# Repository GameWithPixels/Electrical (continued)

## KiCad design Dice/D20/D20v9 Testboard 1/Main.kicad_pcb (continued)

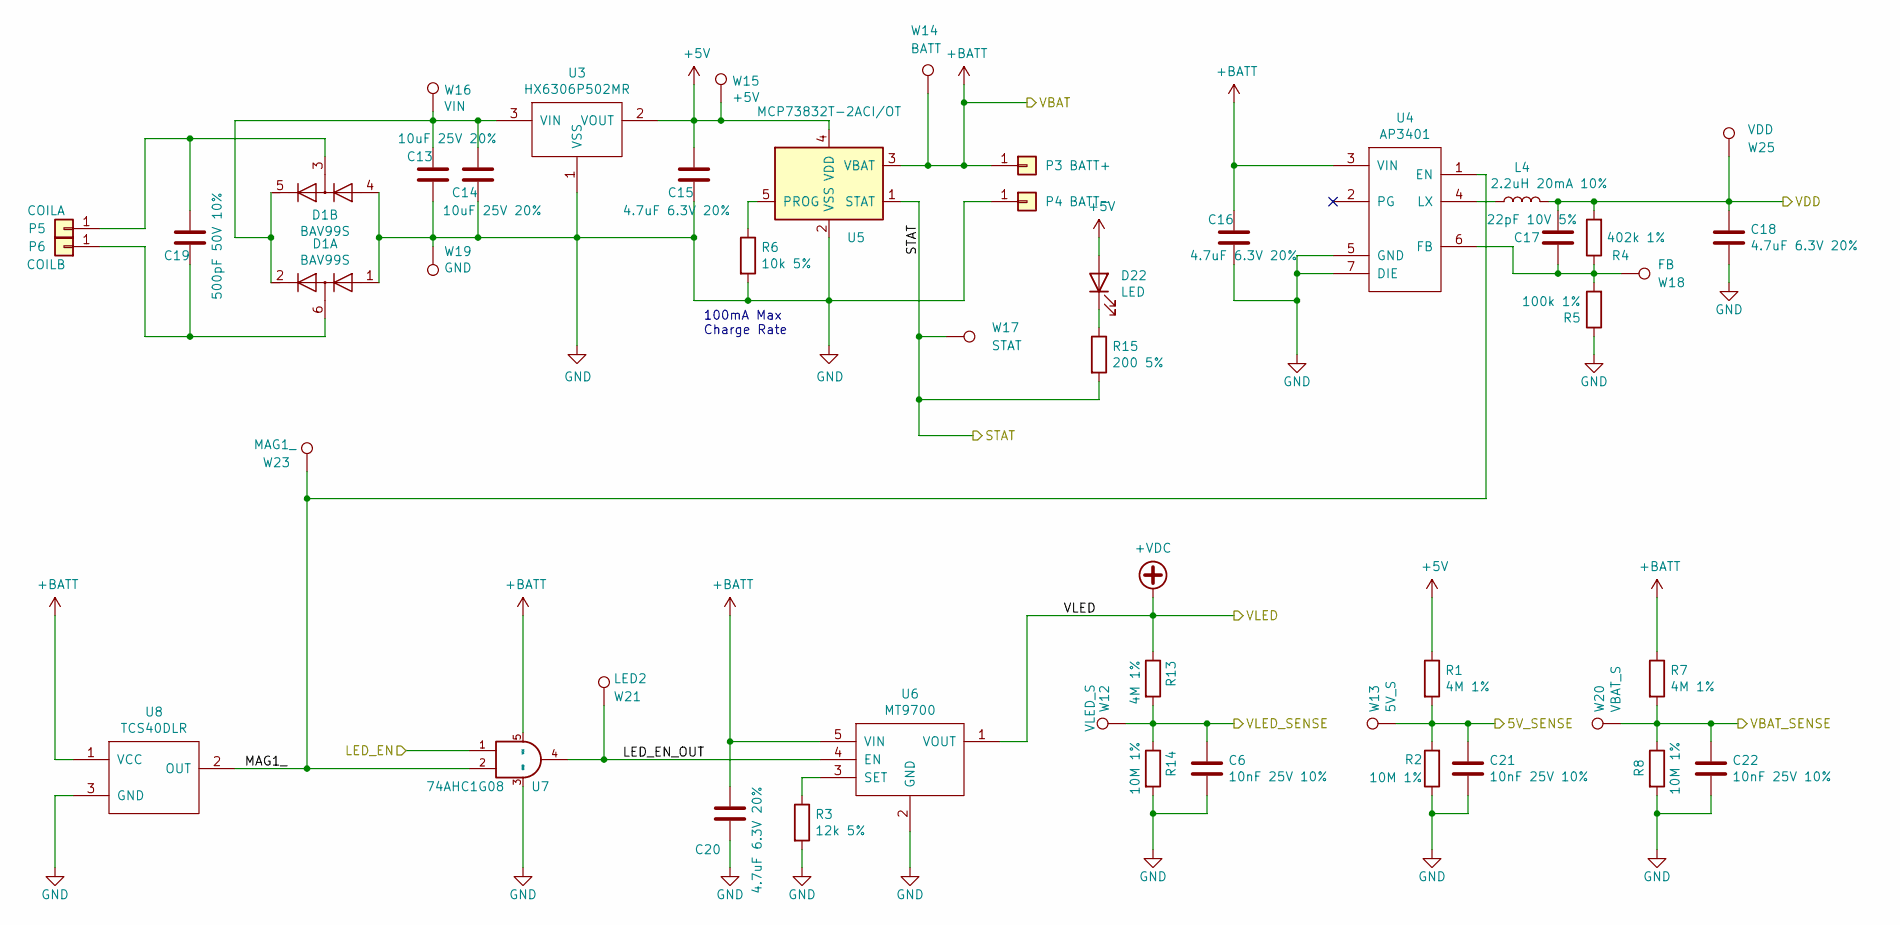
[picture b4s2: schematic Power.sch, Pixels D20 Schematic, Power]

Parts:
C6, C21, C22: 10nF 25V 10%; C_0402_1005Metric; Manufacturer Part Number AC0402KPX7R9BB103
C13, C14: 10uF 25V 20%; C_0805_2012Metric; Manufacturer Part Number CL21A106KAYNNNG
C15, C16, C18, C20: 4.7uF 6.3V 20%; C_0603_1608Metric; Manufacturer Part Number CL10A475MQ8NNNC
C17: 22pF 10V 5%; C_0402_1005Metric; Manufacturer Part Number CC0402JRNPO9BN220
C19: 500pF 50V 10%; C_0402_1005Metric; Manufacturer Part Number 04025C501KAT2A
D1: BAV99S; SOT-363_SC-70-6; Manufacturer Part Number BAV99SH6327XTSA1
D22: LED; LED_0402_1005Metric; Manufacturer Part Number IR19-21C/TR8
L4: 2.2uH 20mA 10%; L_0805_2012Metric; Manufacturer Part Number CV201210-2R2K
P3: BATT+; BatteryConnector
P4: BATT-; BatteryConnector
P5: COILA; TestPoint_THTPad_D1.5mm_Drill0.7mm
P6: COILB; TestPoint_THTPad_D1.5mm_Drill0.7mm
R1, R7, R13: 4M 1%; R_0402_1005Metric; Manufacturer Part Number CRCW04024M02FKED
R2, R8, R14: 10M 1%; R_0402_1005Metric; Manufacturer Part Number SFR01MZPJ106
R3: 12k 5%; R_0402_1005Metric; Manufacturer Part Number RCS040212K0FKED
R4: 402k 1%; R_0402_1005Metric; Manufacturer Part Number ERJ-2RKF4023X
R5: 100k 1%; R_0402_1005Metric; Manufacturer Part Number CRCW0402100KFKEDC
R6: 10k 5%; R_0402_1005Metric; Manufacturer Part Number CRCW040210K0FKEDC
R15: 200 5%; R_0402_1005Metric; Manufacturer Part Number CRCW0402200RJNED
U3: HX6306P502MR; SOT-23; Manufacturer Part Number HX6306P502MR
U4: AP3401; DFN-6-1EP_2x2mm_P0.65mm_EP1x1.6mm; Manufacturer Part Number AP3401DNTR-G1
U5: MCP73832T-2ACI/OT; SOT-23-5; Manufacturer Part Number MCP73832T-2ACI/OT
U6: MT9700; SOT-23-5; Manufacturer Part Number MT9700
U7: 74AHC1G08; SOT-353_SC-70-5; Manufacturer Part Number SN74AHC1G08DCKR
U8: TCS40DLR; SOT-23; Manufacturer Part Number TCS40DLR,LF
W12: VLED_S; TEST_PIN
W13: 5V_S; TEST_PIN
W14: BATT; TEST_PIN
W15: +5V; TEST_PIN
W16: VIN; TEST_PIN
W17: STAT; TEST_PIN
W18: FB; TEST_PIN
W19: GND; TEST_PIN
W20: VBAT_S; TEST_PIN
W21: LED2; TEST_PIN
W23: MAG1_; TEST_PIN
W25: VDD; TEST_PIN

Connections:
+5V: C15.1, D22.2 (A), R1.1, U3.2 (VOUT), U5.4 (VDD), W15.1
/5V_SENSE: C21.1, R1.2, R2.2, W13.1; also elsewhere on the board
/LED_EN: U7.1; also elsewhere on the board
/Power/LED_EN_OUT: U6.4 (EN), U7.4, W21.1
/Power/MAG1_: U4.1 (EN), U7.2, U8.2 (OUT), W23.1
/STATS: R15.2, U5.1 (STAT), W17.1; also elsewhere on the board
/VBAT_SENSE: C22.1, R7.2, R8.1, W20.1; also elsewhere on the board
/VLED_SENSE: C6.1, R13.2, R14.1, W12.1; also elsewhere on the board
GND: C6.2, C13.2, C14.2, C15.2, C16.2, C18.2, C20.2, C21.2, C22.2, D1.1 (A1), D1.4 (A3), P4.1, R2.1, R3.2, R5.1, R6.2, R8.2, R14.2, U3.1 (VSS), U4.5 (GND), U4.7 (DIE), U5.2 (VSS), U6.2 (GND), U7.3 (GND), U8.3 (GND), W19.1; also elsewhere on the board
unnamed: C13.1, C14.1, D1.2 (K2), D1.5 (K4), U3.3 (VIN), W16.1
unnamed: C17.2, R4.1, R5.2, U4.6 (FB), W18.1
unnamed: C19.1, D1.3 (K1A2), P5.1
unnamed: C19.2, D1.6 (K3A4), P6.1
unnamed: D22.1 (K), R15.1
unnamed: L4.1, U4.4 (LX)
unnamed: R3.1, U6.3 (SET)
unnamed: R6.1, U5.5 (PROG)
VBAT: C16.1, C20.1, P3.1, R7.1, U4.3 (VIN), U5.3 (VBAT), U6.5 (VIN), U7.5 (VCC), U8.1 (VCC), W14.1; also elsewhere on the board
VDD: C17.1, C18.1, L4.2, R4.2, W25.1; also elsewhere on the board
VLED: R13.1, U6.1 (VOUT); also elsewhere on the board

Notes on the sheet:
100mA Max Charge Rate

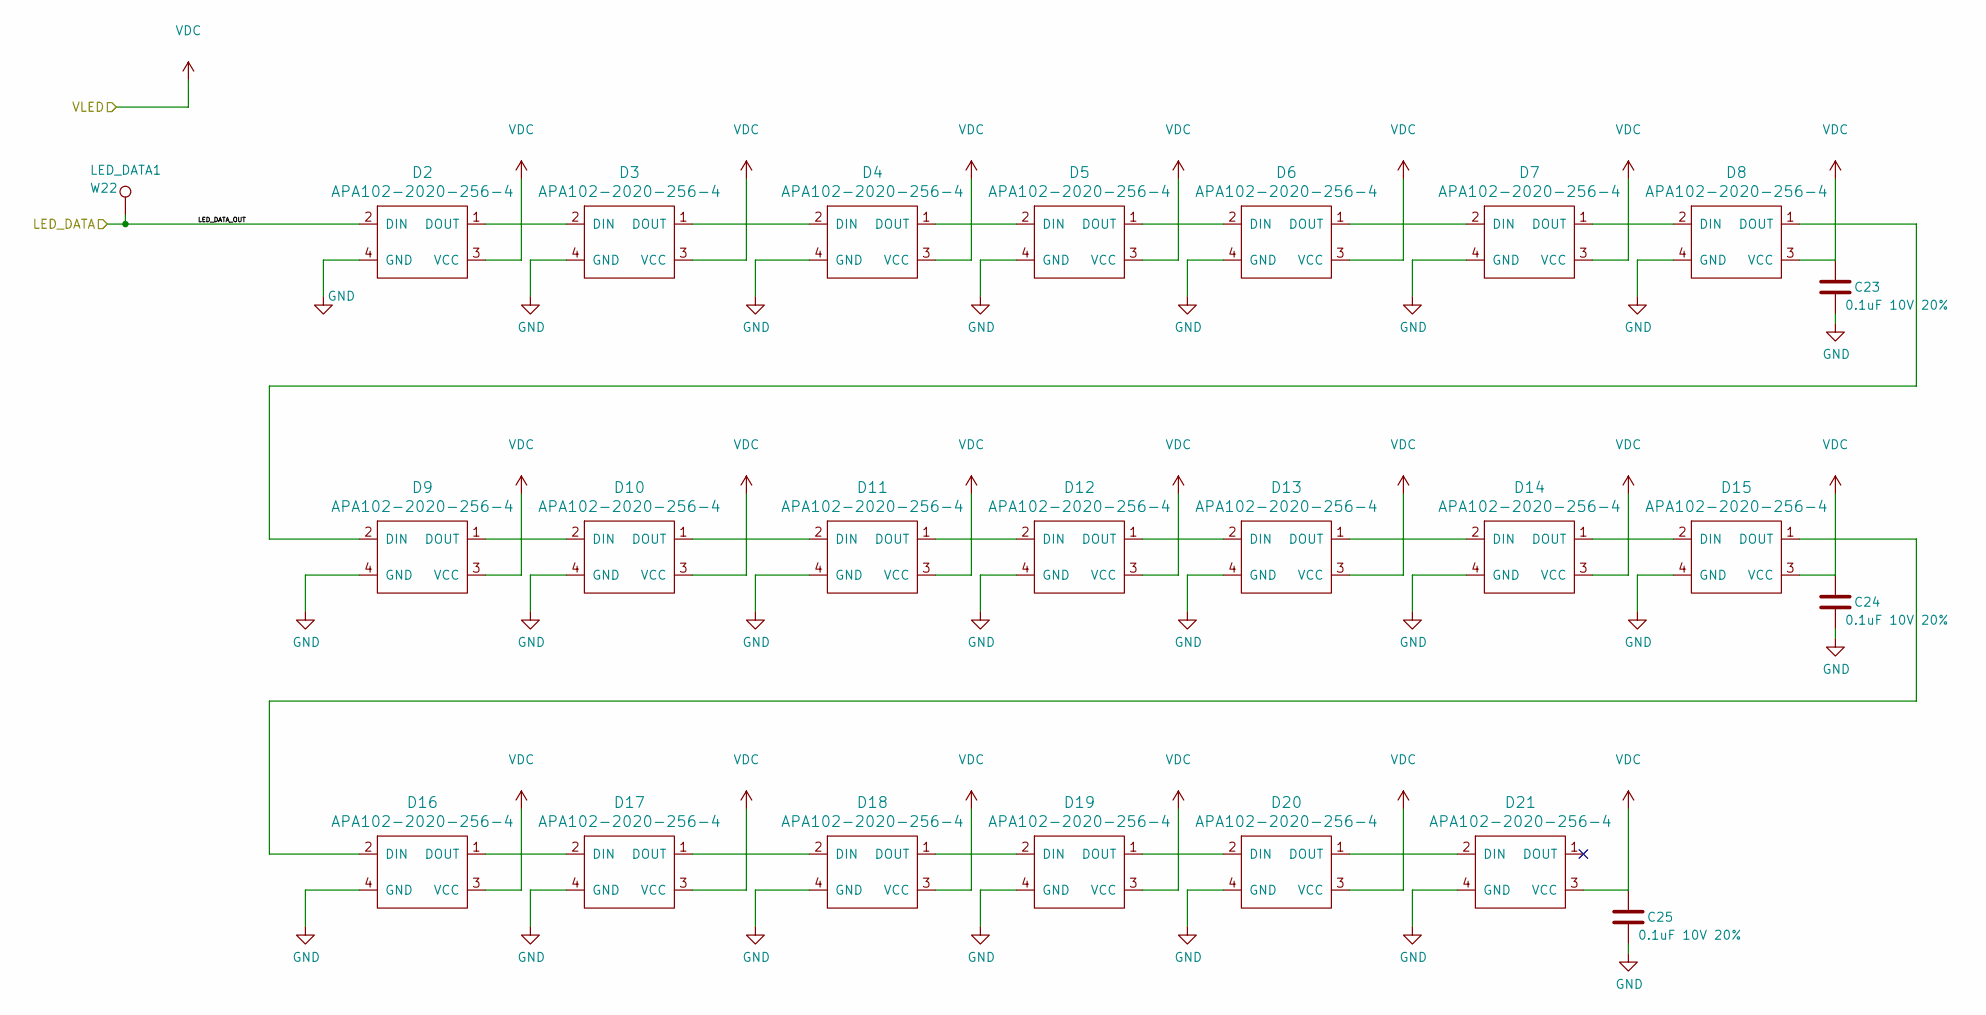
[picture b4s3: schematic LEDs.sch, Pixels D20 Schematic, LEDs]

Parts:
C23, C24, C25: 0.1uF 10V 20%; C_0402_1005Metric; Manufacturer Part Number GRM155R61H104KE19D
D2, D3, D4, D5, D6, D7, D8, D9, D10, D11, D12, D13, D14, D15, D16, D17, D18, D19, D20, D21: APA102-2020-256-4; Manufacturer Part Number APA-102-2020
W22: LED_DATA1; TEST_PIN

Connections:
/LED_DATA: D2.2 (DIN), W22.1; also elsewhere on the board
GND: C23.2, C24.2, C25.2, D2.4 (GND), D3.4 (GND), D4.4 (GND), D5.4 (GND), D6.4 (GND), D7.4 (GND), D8.4 (GND), D9.4 (GND), D10.4 (GND), D11.4 (GND), D12.4 (GND), D13.4 (GND), D14.4 (GND), D15.4 (GND), D16.4 (GND), D17.4 (GND), D18.4 (GND), D19.4 (GND), D20.4 (GND), D21.4 (GND); also elsewhere on the board
unnamed: D2.1 (DOUT), D3.2 (DIN)
unnamed: D3.1 (DOUT), D4.2 (DIN)
unnamed: D4.1 (DOUT), D5.2 (DIN)
unnamed: D5.1 (DOUT), D6.2 (DIN)
unnamed: D6.1 (DOUT), D7.2 (DIN)
unnamed: D7.1 (DOUT), D8.2 (DIN)
unnamed: D8.1 (DOUT), D9.2 (DIN)
unnamed: D10.1 (DOUT), D11.2 (DIN)
unnamed: D9.1 (DOUT), D10.2 (DIN)
unnamed: D11.1 (DOUT), D12.2 (DIN)
unnamed: D12.1 (DOUT), D13.2 (DIN)
unnamed: D13.1 (DOUT), D14.2 (DIN)
unnamed: D14.1 (DOUT), D15.2 (DIN)
unnamed: D15.1 (DOUT), D16.2 (DIN)
unnamed: D16.1 (DOUT), D17.2 (DIN)
unnamed: D17.1 (DOUT), D18.2 (DIN)
unnamed: D18.1 (DOUT), D19.2 (DIN)
unnamed: D19.1 (DOUT), D20.2 (DIN)
unnamed: D20.1 (DOUT), D21.2 (DIN)
VLED: C23.1, C24.1, C25.1, D2.3 (VCC), D3.3 (VCC), D4.3 (VCC), D5.3 (VCC), D6.3 (VCC), D7.3 (VCC), D8.3 (VCC), D9.3 (VCC), D10.3 (VCC), D11.3 (VCC), D12.3 (VCC), D13.3 (VCC), D14.3 (VCC), D15.3 (VCC), D16.3 (VCC), D17.3 (VCC), D18.3 (VCC), D19.3 (VCC), D20.3 (VCC), D21.3 (VCC); also elsewhere on the board

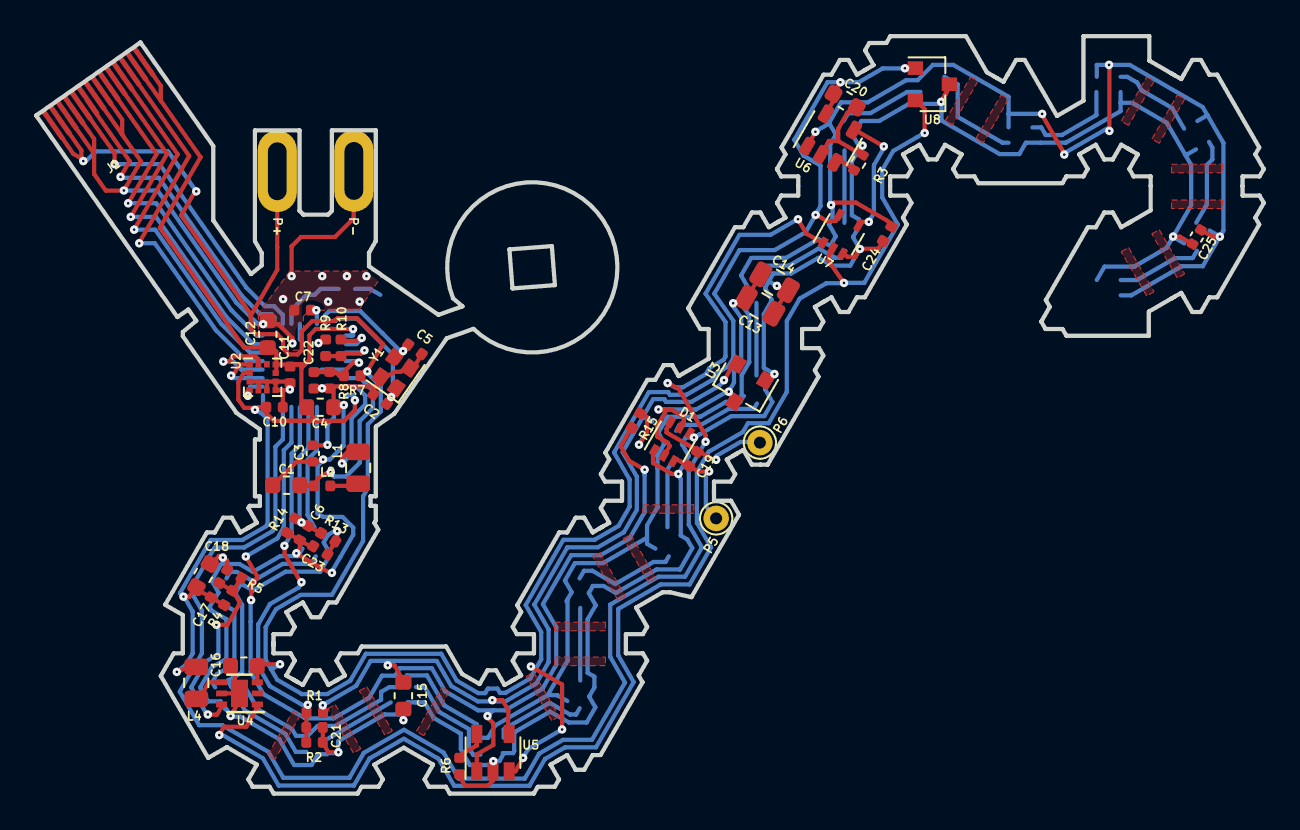
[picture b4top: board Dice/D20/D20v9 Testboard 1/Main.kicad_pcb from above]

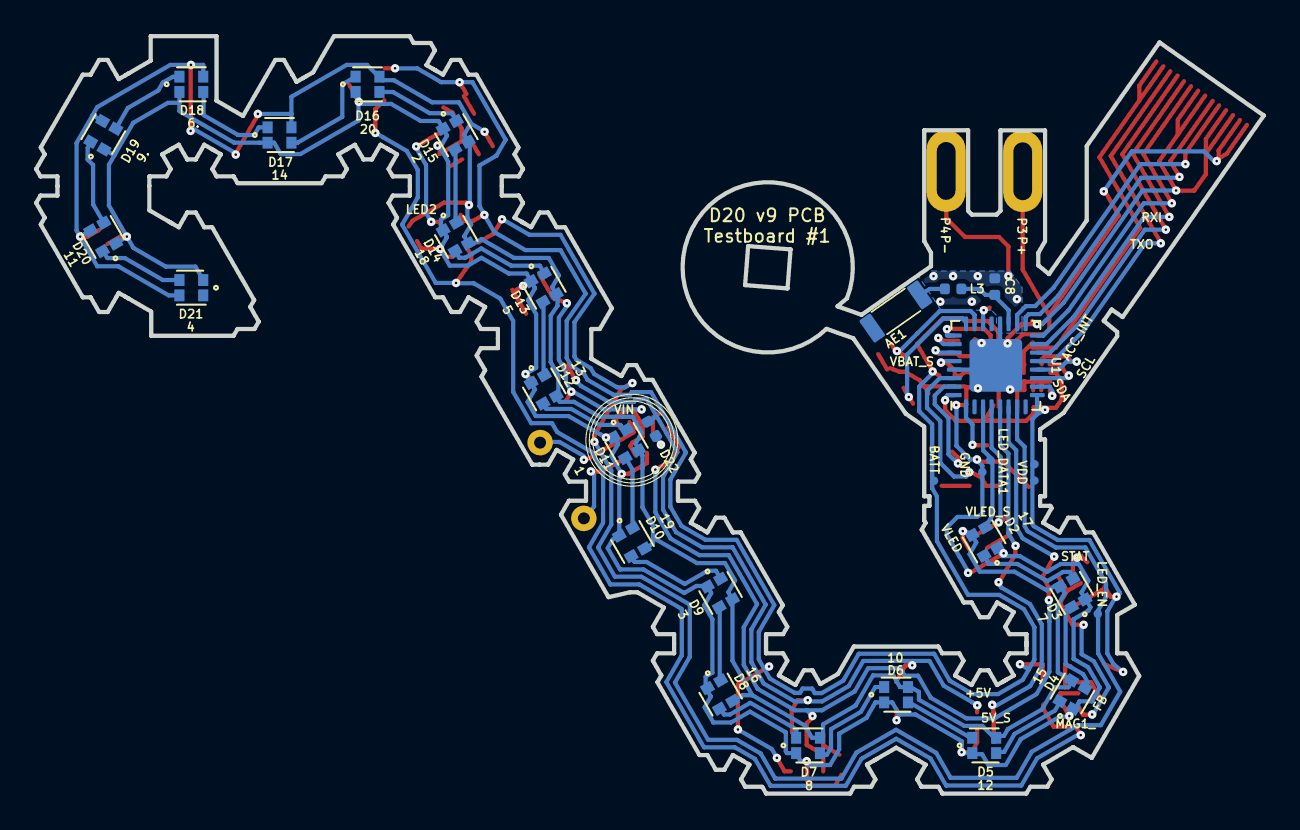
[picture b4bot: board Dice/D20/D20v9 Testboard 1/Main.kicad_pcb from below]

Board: 2 copper layers, 72.1 x 44.5 mm, 100 parts (49 on the bottom side), 60 nets.
